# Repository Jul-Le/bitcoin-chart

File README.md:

# bitcoin-chart
Bitcoin price chart to ST7735R LCD display using ESP8266 and Arduino.

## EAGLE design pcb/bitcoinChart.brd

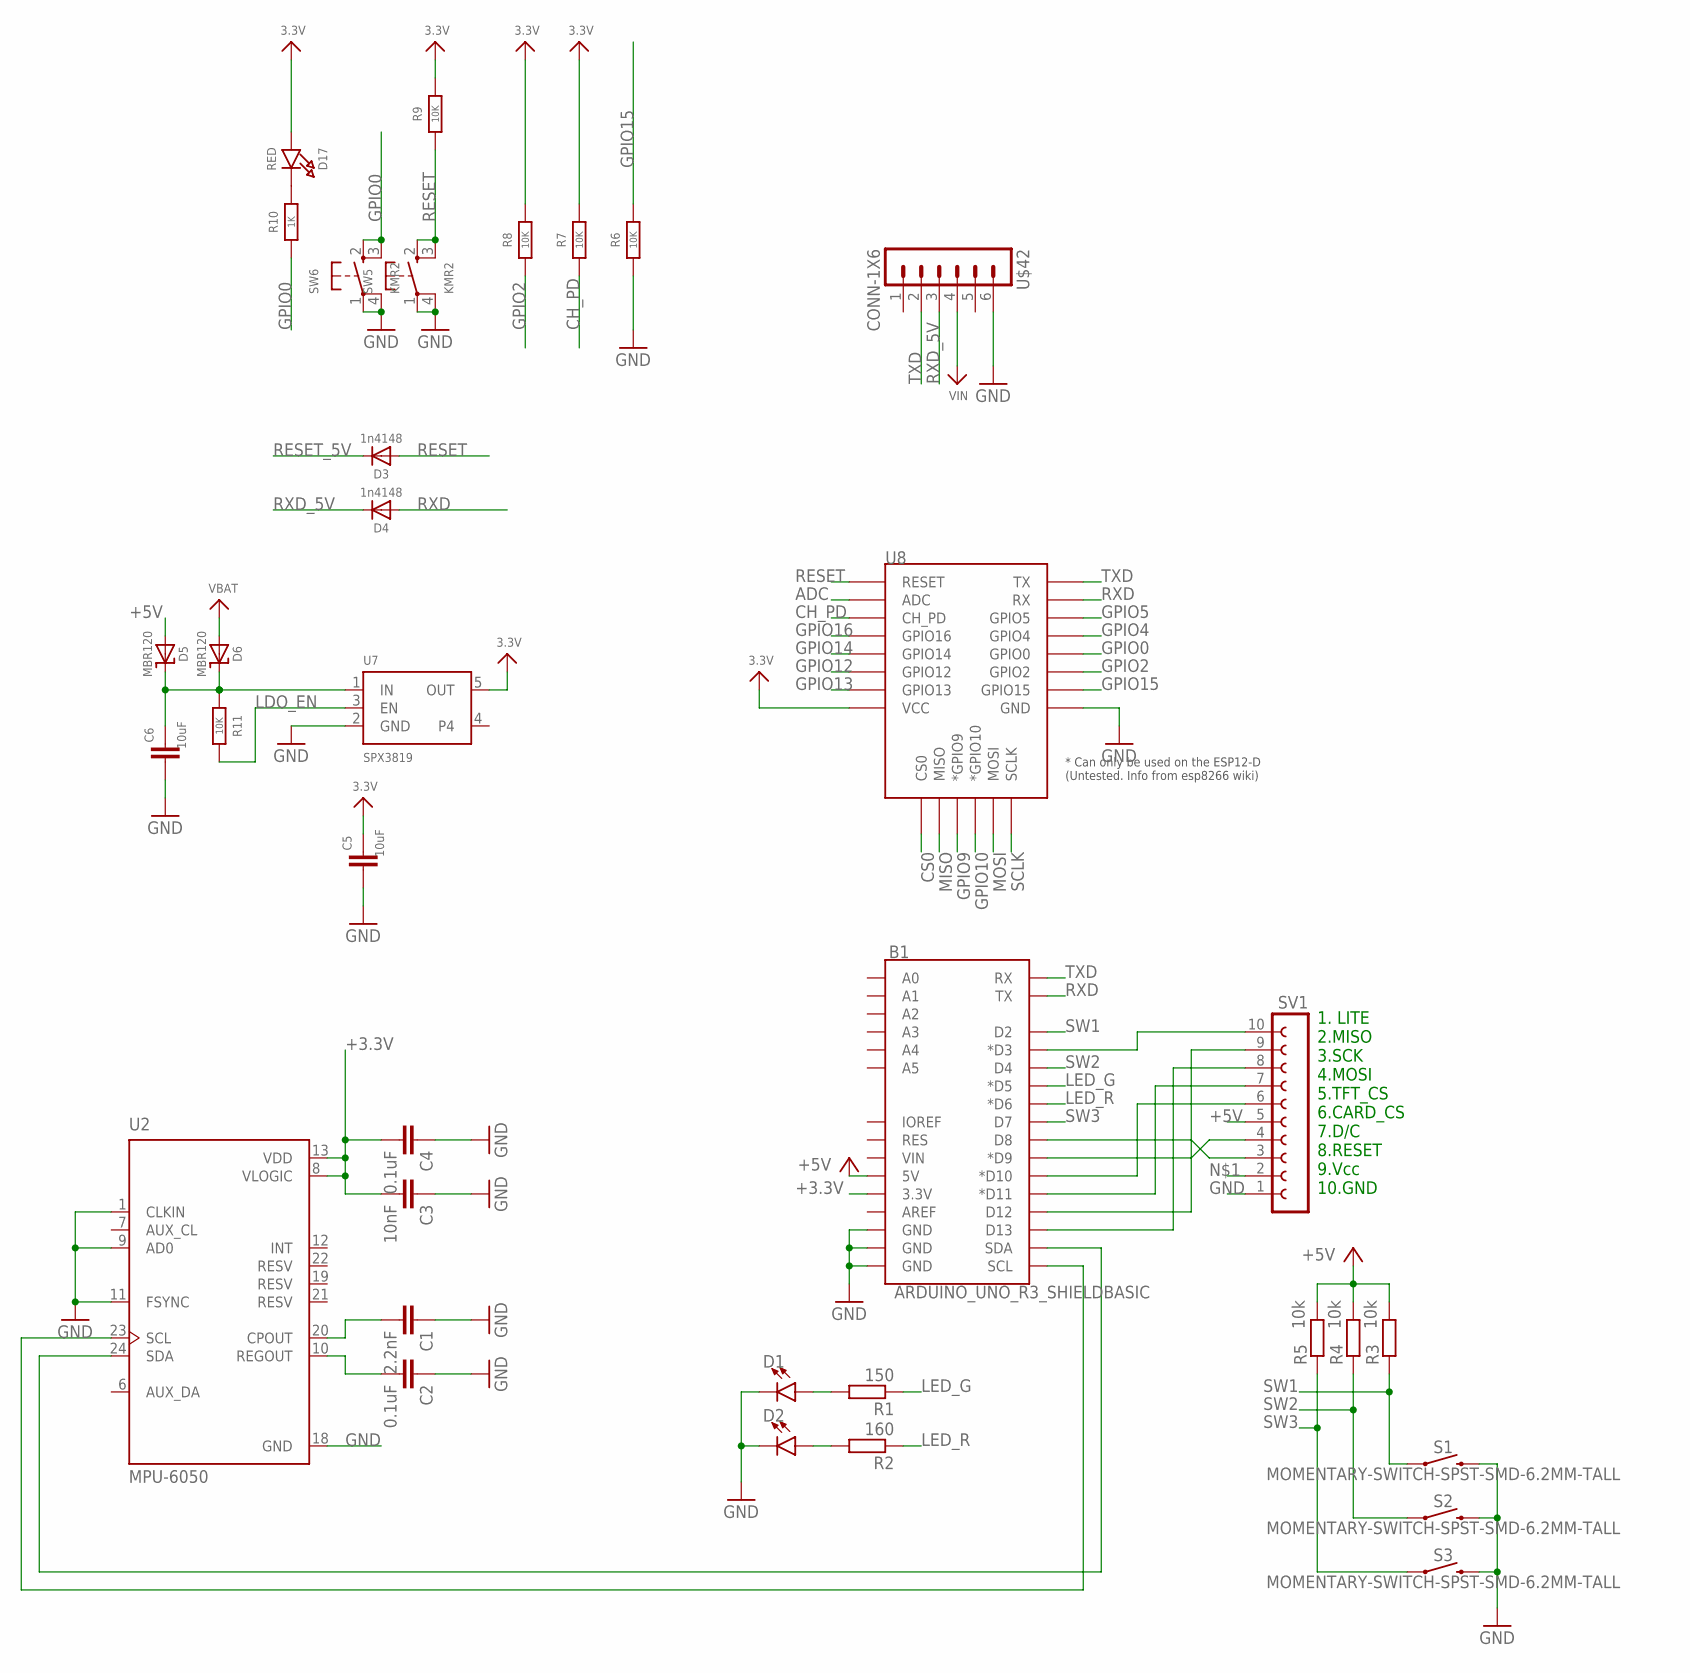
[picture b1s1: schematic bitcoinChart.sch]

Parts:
B1: ARDUINO_UNO_R3_SHIELDBASIC; UNO_R3_SHIELD
C1: 2.2nF; C1206K
C2, C4: 0.1uF; C1206K
C3: 10nF; C1206K
C5, C6: 10uF; C0805K
D1: GREEN; CHIPLED_0805
D2: RED; CHIPLED_0805
D3, D4: 1n4148; SOD-323
D5, D6: MBR120; SOD-123
D17: RED; LED_0805
R1: 150; M1206
R2: 160; M1206
R3, R4, R5: 10k; M1206
R6, R7, R8, R9, R11: 10K; R0805
R10: 1K; R0805
S1, S2, S3: MOMENTARY-SWITCH-SPST-SMD-6.2MM-TALL; TACTILE_SWITCH_SMD_6.2MM_TALL
SV1: FE10-1; FE10
SW5, SW6: KMR2; BTN_KMR2
U2: MPU-6050; QFN50P400X400X95-24N
U7: SPX3819; SOT-23-5
U8: ESP12ESMD; ESP12E-SMD
U$42: CONN-1X6; GHI-HEADERS_TH-1X6

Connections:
3.3V: C5.1, D17.A, R7.2, R8.2, R9.2, U7.5 (OUT), U8.VCC
+3.3V: B1.3.3V, C3.2, C4.2, U2.8 (VLOGIC), U2.13 (VDD)
+5V: B1.5V, D5.2 (A), R3.2, R4.2, R5.2, SV1.5
ADC: U8.ADC
CH_PD: R7.1, U8.CH_PD
CS0: U8.CS0
GND: B1.GND@0 (GND), B1.GND@1 (GND), B1.GND@2 (GND), C1.1, C2.1, C3.1, C4.1, C5.2, C6.2, D1.C, D2.C, R6.1, S1.B2 (2), S2.B2 (2), S3.B2 (2), SV1.1, SW5.1, SW5.4 (P1), SW6.1, SW6.4 (P1), U2.1 (CLKIN), U2.9 (AD0), U2.11 (FSYNC), U2.18 (GND), U7.2 (GND), U8.GND, U$42.6
GPIO0: R10.1, SW6.2 (S), SW6.3 (S1), U8.GPIO0
GPIO2: R8.1, U8.GPIO2
GPIO4: U8.GPIO4
GPIO5: U8.GPIO5
GPIO9: U8.GPIO9 (*GPIO9)
GPIO10: U8.GPIO10 (*GPIO10)
GPIO12: U8.GPIO12
GPIO13: U8.GPIO13
GPIO14: U8.GPIO14
GPIO15: R6.2, U8.GPIO15
GPIO16: U8.GPIO16
LDO_EN: R11.2, U7.3 (EN)
LED_G: B1.D5 (*D5), R1.1
LED_R: B1.D6 (*D6), R2.1
MISO: U8.MISO
MOSI: U8.MOSI
unnamed: B1.SCL, U2.23 (SCL)
unnamed: B1.SDA, U2.24 (SDA)
unnamed: B1.D3 (*D3), SV1.10
unnamed: B1.D8, SV1.3
unnamed: B1.D13, SV1.8
unnamed: B1.D11 (*D11), SV1.7
unnamed: B1.D10 (*D10), SV1.6
unnamed: B1.D9 (*D9), SV1.4
unnamed: C2.2, U2.10 (REGOUT)
unnamed: C1.2, U2.20 (CPOUT)
unnamed: B1.D12, SV1.9
unnamed: D1.A, R1.2
unnamed: C6.1, D5.1 (C), D6.1 (C), R11.1, U7.1 (IN)
unnamed: D17.K (C), R10.2
unnamed: D2.A, R2.2
RESET: D3.2 (A), R9.1, SW5.2 (S), SW5.3 (S1), U8.RESET
RESET_5V: D3.1 (C)
RXD: B1.TX, D4.2 (A), U8.RXD0 (RX)
RXD_5V: D4.1 (C), U$42.3
SCLK: U8.SCLK
SW1: B1.D2, R3.1, S1.A2 (1)
SW2: B1.D4, R4.1, S2.A2 (1)
SW3: B1.D7, R5.1, S3.A2 (1)
TXD: B1.RX, U8.TXD0 (TX), U$42.2
VBAT: D6.2 (A)
VIN: U$42.4

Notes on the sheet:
1. LITE 2.MISO 3.SCK 4.MOSI 5.TFT_CS 6.CARD_CS 7.D/C 8.RESET 9.Vcc 10.GND

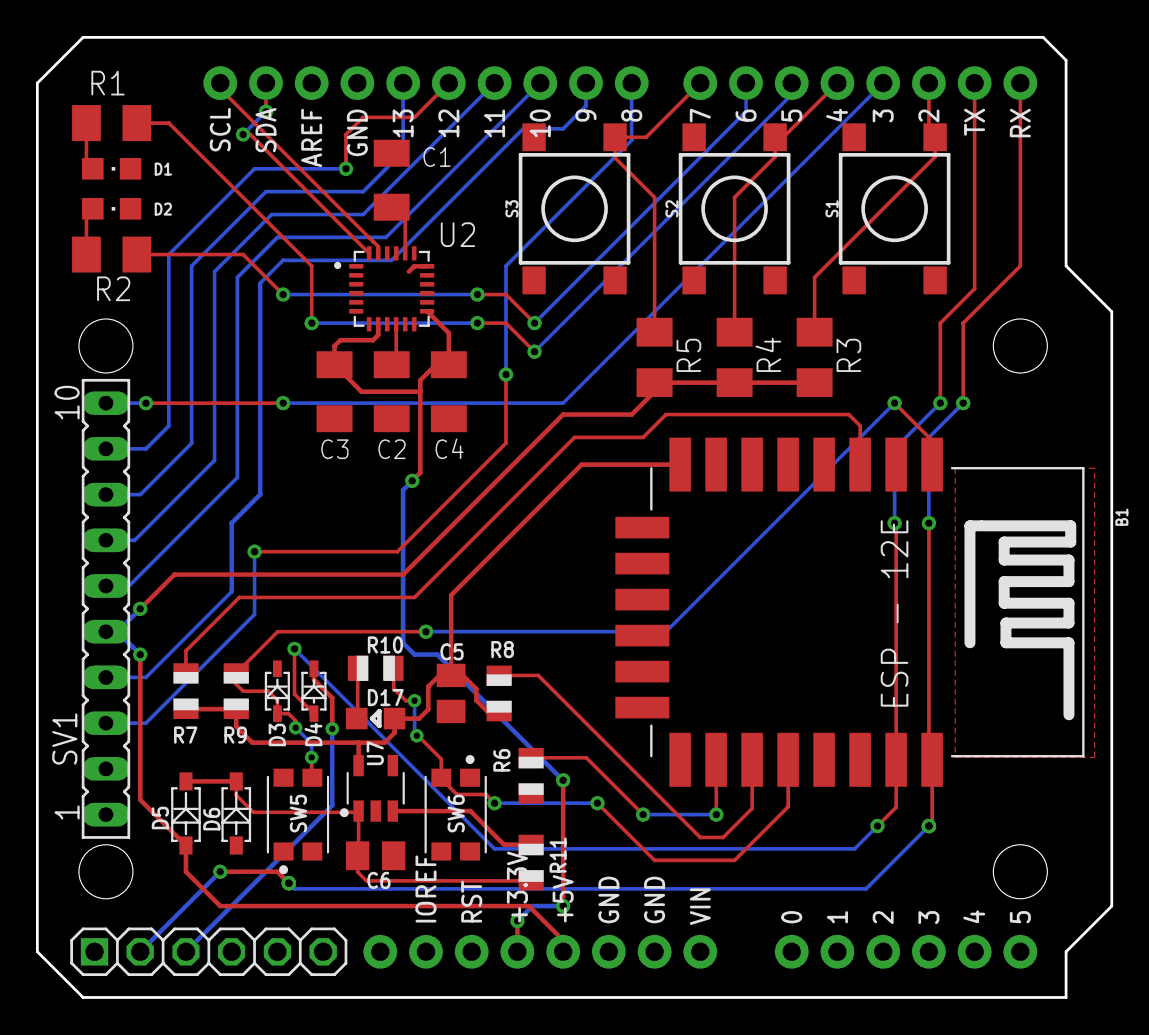
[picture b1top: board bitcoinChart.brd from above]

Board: 2 copper layers, 59.7 x 53.3 mm, 35 parts (0 on the bottom side), 33 nets.

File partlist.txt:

Partlist

Exported from bitcoinChart.sch at 24.1.2019 17.10

EAGLE Version 9.3.0 Copyright (c) 1988-2019 Autodesk, Inc.

Assembly variant: 

Part     Value                                Device                               Package                       Library           Sheet

B1       ARDUINO_UNO_R3_SHIELDBASIC           ARDUINO_UNO_R3_SHIELDBASIC           UNO_R3_SHIELD                 SparkFun-Boards   1
C1       2.2nF                                C-EUC1206K                           C1206K                        resistor          1
C2       0.1uF                                C-EUC1206K                           C1206K                        resistor          1
C3       10nF                                 C-EUC1206K                           C1206K                        resistor          1
C4       0.1uF                                C-EUC1206K                           C1206K                        resistor          1
C5       10uF                                 SMD-CAPACITOR0805                    C0805K                        basic_components  1
C6       10uF                                 SMD-CAPACITOR0805                    C0805K                        basic_components  1
D1       GREEN                                LEDCHIPLED_0805                      CHIPLED_0805                  led               1
D2       RED                                  LEDCHIPLED_0805                      CHIPLED_0805                  led               1
D3       1n4148                               DIODESOD-323                         SOD-323                       basic_components  1
D4       1n4148                               DIODESOD-323                         SOD-323                       basic_components  1
D5       MBR120                               DIODE-SCHOTTKYSOD-123                SOD-123                       basic_components  1
D6       MBR120                               DIODE-SCHOTTKYSOD-123                SOD-123                       basic_components  1
D17      RED                                  LED                                  LED_0805                      basic_components  1
R1       150                                  R-EU_M1206                           M1206                         resistor          1
R2       160                                  R-EU_M1206                           M1206                         resistor          1
R3       10k                                  R-EU_M1206                           M1206                         resistor          1
R4       10k                                  R-EU_M1206                           M1206                         resistor          1
R5       10k                                  R-EU_M1206                           M1206                         resistor          1
R6       10K                                  SMD-RESISTORR0805                    R0805                         basic_components  1
R7       10K                                  SMD-RESISTORR0805                    R0805                         basic_components  1
R8       10K                                  SMD-RESISTORR0805                    R0805                         basic_components  1
R9       10K                                  SMD-RESISTORR0805                    R0805                         basic_components  1
R10      1K                                   SMD-RESISTORR0805                    R0805                         basic_components  1
R11      10K                                  SMD-RESISTORR0805                    R0805                         basic_components  1
S1       MOMENTARY-SWITCH-SPST-SMD-6.2MM-TALL MOMENTARY-SWITCH-SPST-SMD-6.2MM-TALL TACTILE_SWITCH_SMD_6.2MM_TALL SparkFun-Switches 1
S2       MOMENTARY-SWITCH-SPST-SMD-6.2MM-TALL MOMENTARY-SWITCH-SPST-SMD-6.2MM-TALL TACTILE_SWITCH_SMD_6.2MM_TALL SparkFun-Switches 1
S3       MOMENTARY-SWITCH-SPST-SMD-6.2MM-TALL MOMENTARY-SWITCH-SPST-SMD-6.2MM-TALL TACTILE_SWITCH_SMD_6.2MM_TALL SparkFun-Switches 1
SV1                                           FE10-1                               FE10                          untitled          1
SW5      KMR2                                 BUTTON_KMR2KMR2                      BTN_KMR2                      basic_components  1
SW6      KMR2                                 BUTTON_KMR2KMR2                      BTN_KMR2                      basic_components  1
U$42     CONN-1X6                             CONN-1X6                             GHI-HEADERS_TH-1X6            basic_components  1
U2       MPU-6050                             MPU-6050                             QFN50P400X400X95-24N          MPU-6050          1
U7       SPX3819                              MIC5219SOT-23-5                      SOT-23-5                      basic_components  1
U8                                            ESP12ESMD                            ESP12E-SMD                    basic_components  1

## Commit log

2019-01-02 Added components
2019-01-03 Completed PCB
2019-01-03 Changed LED package, removed routing over antenna
2019-01-03 Picture, connected some pins on MPU6050
2019-01-07 Added MISO
2019-01-07 Updated manufacturing image
2019-01-24 partlist
2019-01-24 partlist updated
2019-02-07 Graph
2019-02-21 Graph class

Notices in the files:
parts and their libraries:
SparkFun-Boards: Licensing: Creative Commons ShareAlike 4.0 International - https://creativecommons.org/licenses/by-sa/4.0
microbuilder: This work is placed in the public domain, and may be freely used for commercial and non-commercial work with the following conditions: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
